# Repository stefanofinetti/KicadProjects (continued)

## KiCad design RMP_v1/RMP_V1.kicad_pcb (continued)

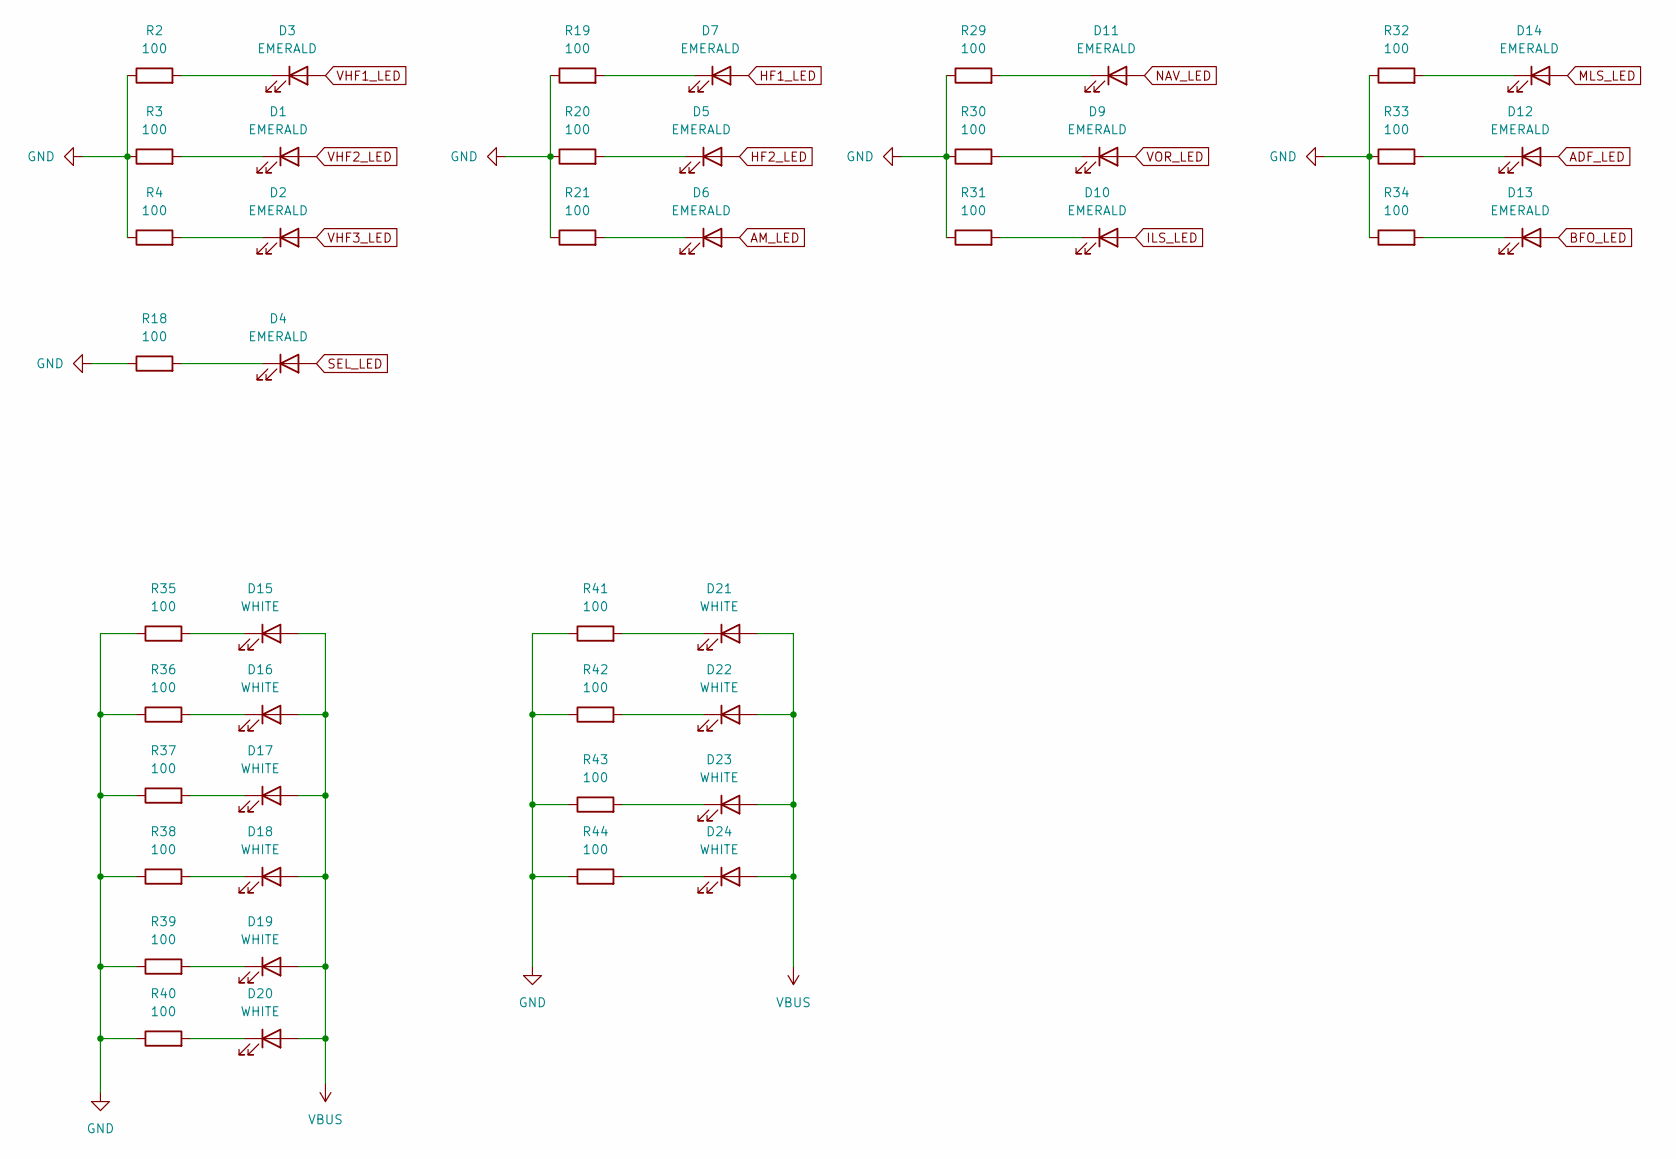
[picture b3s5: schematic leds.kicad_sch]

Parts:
D1, D2, D3, D4, D5, D6, D7, D9, D10, D11, D12, D13, D14: EMERALD; LED_0805_2012Metric
D15, D16, D17, D18, D19, D20, D21, D22, D23, D24: WHITE; LED_0603_1608Metric
R2, R3, R4, R18, R19, R20, R21, R29, R30, R31, R32, R33, R34, R35, R36, R37, R38, R39, R40, R41, R42, R43, R44: 100; R_0402_1005Metric

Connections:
ADF_LED: D12.2 (A); also elsewhere on the board
AM_LED: D6.2 (A); also elsewhere on the board
BFO_LED: D13.2 (A); also elsewhere on the board
GND: R2.1, R3.1, R4.1, R18.1, R19.1, R20.1, R21.1, R29.1, R30.1, R31.1, R32.1, R33.1, R34.1, R35.1, R36.1, R37.1, R38.1, R39.1, R40.1, R41.1, R42.1, R43.1, R44.1; also elsewhere on the board
HF1_LED: D7.2 (A); also elsewhere on the board
HF2_LED: D5.2 (A); also elsewhere on the board
ILS_LED: D10.2 (A); also elsewhere on the board
MLS_LED: D14.2 (A); also elsewhere on the board
NAV_LED: D11.2 (A); also elsewhere on the board
unnamed: D1.1 (K), R3.2
unnamed: D2.1 (K), R4.2
unnamed: D3.1 (K), R2.2
unnamed: D4.1 (K), R18.2
unnamed: D5.1 (K), R20.2
unnamed: D6.1 (K), R21.2
unnamed: D7.1 (K), R19.2
unnamed: D9.1 (K), R30.2
unnamed: D10.1 (K), R31.2
unnamed: D11.1 (K), R29.2
unnamed: D12.1 (K), R33.2
unnamed: D13.1 (K), R34.2
unnamed: D14.1 (K), R32.2
unnamed: D15.1 (K), R35.2
unnamed: D16.1 (K), R36.2
unnamed: D17.1 (K), R37.2
unnamed: D18.1 (K), R38.2
unnamed: D19.1 (K), R39.2
unnamed: D20.1 (K), R40.2
unnamed: D21.1 (K), R41.2
unnamed: D22.1 (K), R42.2
unnamed: D23.1 (K), R43.2
unnamed: D24.1 (K), R44.2
SEL_LED: D4.2 (A); also elsewhere on the board
VBUS: D15.2 (A), D16.2 (A), D17.2 (A), D18.2 (A), D19.2 (A), D20.2 (A), D21.2 (A), D22.2 (A), D23.2 (A), D24.2 (A); also elsewhere on the board
VHF1_LED: D3.2 (A); also elsewhere on the board
VHF2_LED: D1.2 (A); also elsewhere on the board
VHF3_LED: D2.2 (A); also elsewhere on the board
VOR_LED: D9.2 (A); also elsewhere on the board

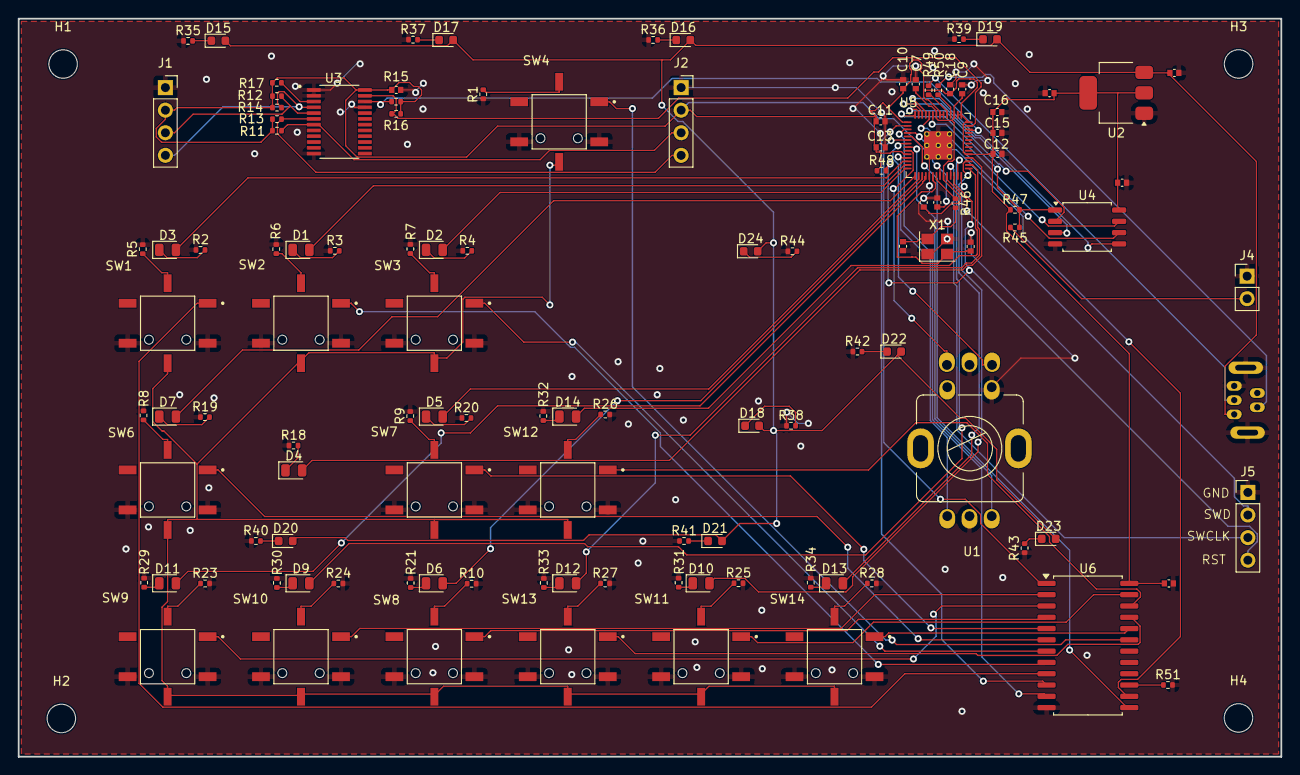
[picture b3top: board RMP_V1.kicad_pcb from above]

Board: 2 copper layers, 142.0 x 83.0 mm, 120 parts (1 on the bottom side), 101 nets.

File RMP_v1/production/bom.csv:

Designator,Footprint,Quantity,Value,LCSC Part #
"C1, C10, C11, C12, C13, C14, C15, C16, C17, C5, C7, C8",Perfect_0402,12,100nF,
"C18, C9",Perfect_0402,2,1uF,
"C2, C3",Perfect_0402,2,15pF,
"C4, C6",Perfect_0402,2,10uF,
"D1, D10, D11, D12, D13, D14, D2, D3, D4, D5, D6, D7, D9",0805,13,EMERALD,
"D15, D16, D17, D18, D19, D20, D21, D22, D23, D24",0603,10,WHITE,
J1,PinSocket_1x04_P2.54mm_Vertical,1,VHF Active OLED,
J2,PinSocket_1x04_P2.54mm_Vertical,1,VHF Standby OLED,
J3,USB_B_Mini_Amphenol_UE25BE5510H,1,USB_B_Micro,
J4,PinHeader_1x02_P2.54mm_Vertical,1,Conn_01x02,
J5,PinHeader_1x04_P2.54mm_Vertical,1,RP2040_SWD,
"R1, R10, R18, R19, R2, R20, R21, R23, R24, R25, R26, R27, R28, R29, R3, R30, R31, R32, R33, R34, R35, R36, R37, R38, R39, R4, R40, R41, R42, R43, R44, R5, R6, R7, R8, R9",0402,36,100,
"R11, R12, R13, R14, R15, R16",0402,6,4.7K,
"R17, R48, R51",0402,3,10K,
"R45, R46",0402,2,1k,
R47,0402,1,DNF,
"R49, R50",0402,2,27,
SW1,SW_TL3240F260R,1,VHF1_SW,C4364809
SW10,SW_TL3240F260R,1,VOR,C4364985
SW11,SW_TL3240F260R,1,ILS,C4364985
SW12,SW_TL3240F260R,1,MLS,C4364985
SW13,SW_TL3240F260R,1,ADF,C4364985
SW14,SW_TL3240F260R,1,BFO,C4364985
SW2,SW_TL3240F260R,1,VHF2_SW,C4364809
SW3,SW_TL3240F260R,1,VHF3_SW,C4364809
SW4,SW_TL3240F260R,1,XFER_SW,C4364985
SW6,SW_TL3240F260R,1,HF1,C4364809
SW7,SW_TL3240F260R,1,HF2,C4364809
SW8,SW_TL3240F260R,1,AM,C4364809
SW9,SW_TL3240F260R,1,NAV,C4364985
U1,EC11EBB24C03,1,ENCODER,
U2,SOT-223-3_TabPin2,1,NCP1117-3.3_SOT223,
U3,SOP65P640X120-24N,1,PCA9548APW,
U4,SOIC-8_5.23x5.23mm_P1.27mm,1,W25Q128JVS,
U5,QFN-56-1EP_7x7mm_P0.4mm_EP3.2x3.2mm,1,RP2040,
U6,SOIC-24W_7.5x15.4mm_P1.27mm,1,CD74HC4067M,
X1,Crystal_SMD_3225-4Pin_3.2x2.5mm,1,ABM8-272-T3,

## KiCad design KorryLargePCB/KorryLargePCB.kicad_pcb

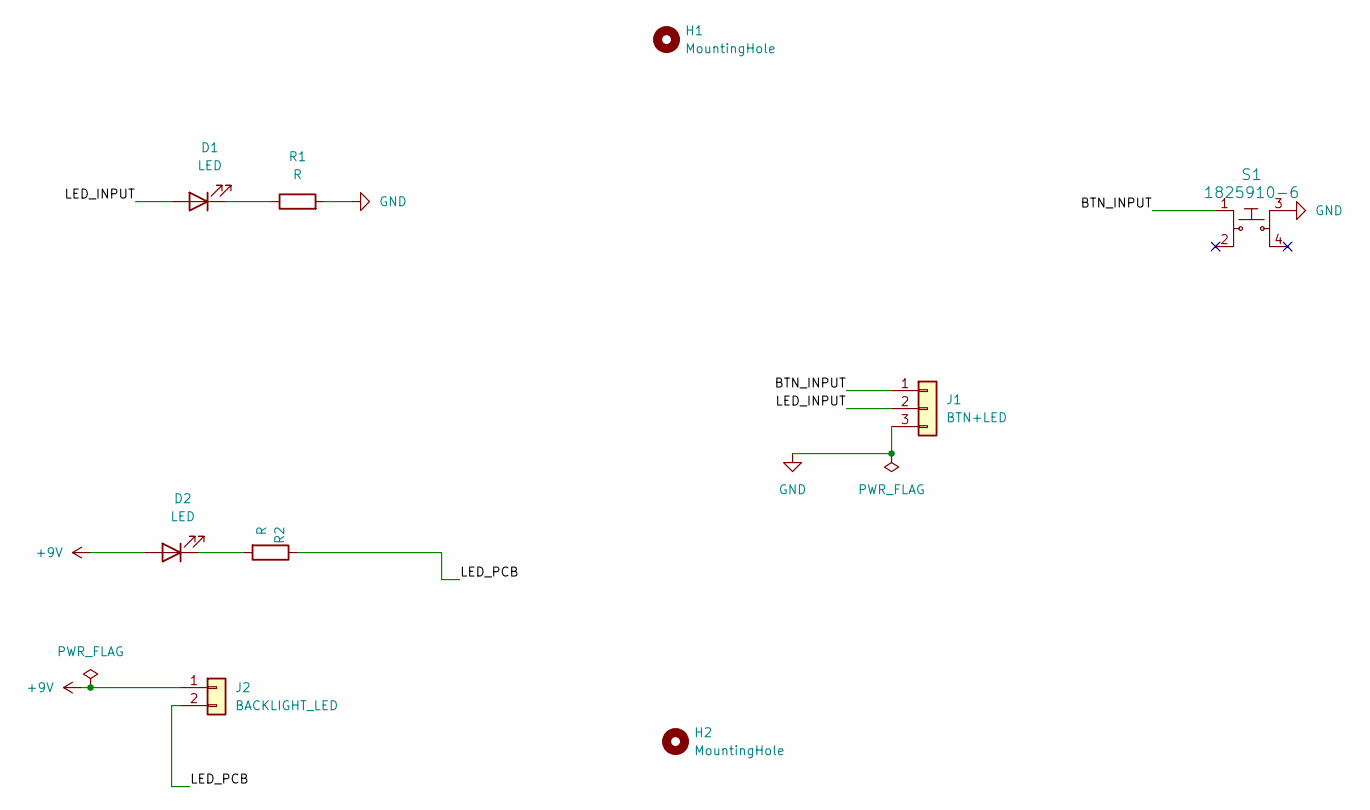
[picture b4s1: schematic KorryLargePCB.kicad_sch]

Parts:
D1, D2: LED; LED_D3.0mm
H1, H2: MountingHole; MountingHole_2.2mm_M2_DIN965_Pad_TopBottom
J1: BTN+LED; JST_EH_B3B-EH-A_1x03_P2.50mm_Vertical
J2: BACKLIGHT_LED; JST_EH_B2B-EH-A_1x02_P2.50mm_Vertical
R1, R2: R; R_Axial_DIN0207_L6.3mm_D2.5mm_P7.62mm_Horizontal
S1: 1825910-6; Switch_Tactile_THT_6x6mm; MPN 1825910-6; Digi-Key_PN 450-1650-ND

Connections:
+9V: D2.2 (A), J2.1
/BTN_INPUT: J1.1, S1.1
/LED_INPUT: D1.2 (A), J1.2
/LED_PCB: J2.2, R2.1
GND: J1.3, R1.2, S1.3
unnamed: D1.1 (K), R1.1
unnamed: D2.1 (K), R2.2

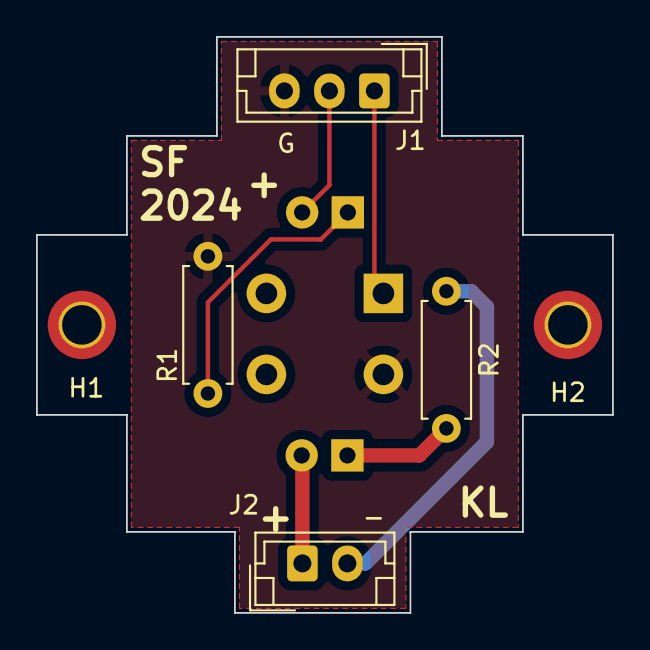
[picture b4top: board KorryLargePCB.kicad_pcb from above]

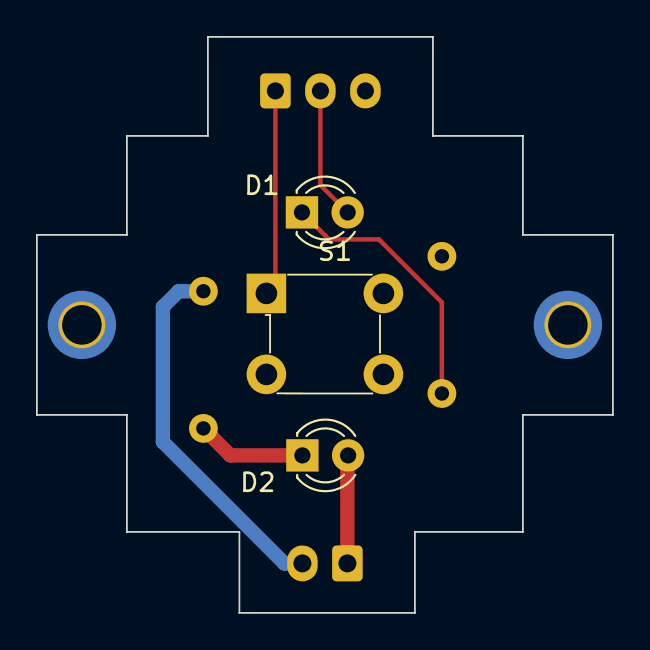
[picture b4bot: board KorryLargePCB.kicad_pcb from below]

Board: 2 copper layers, 32.0 x 32.0 mm, 9 parts (3 on the bottom side), 7 nets.

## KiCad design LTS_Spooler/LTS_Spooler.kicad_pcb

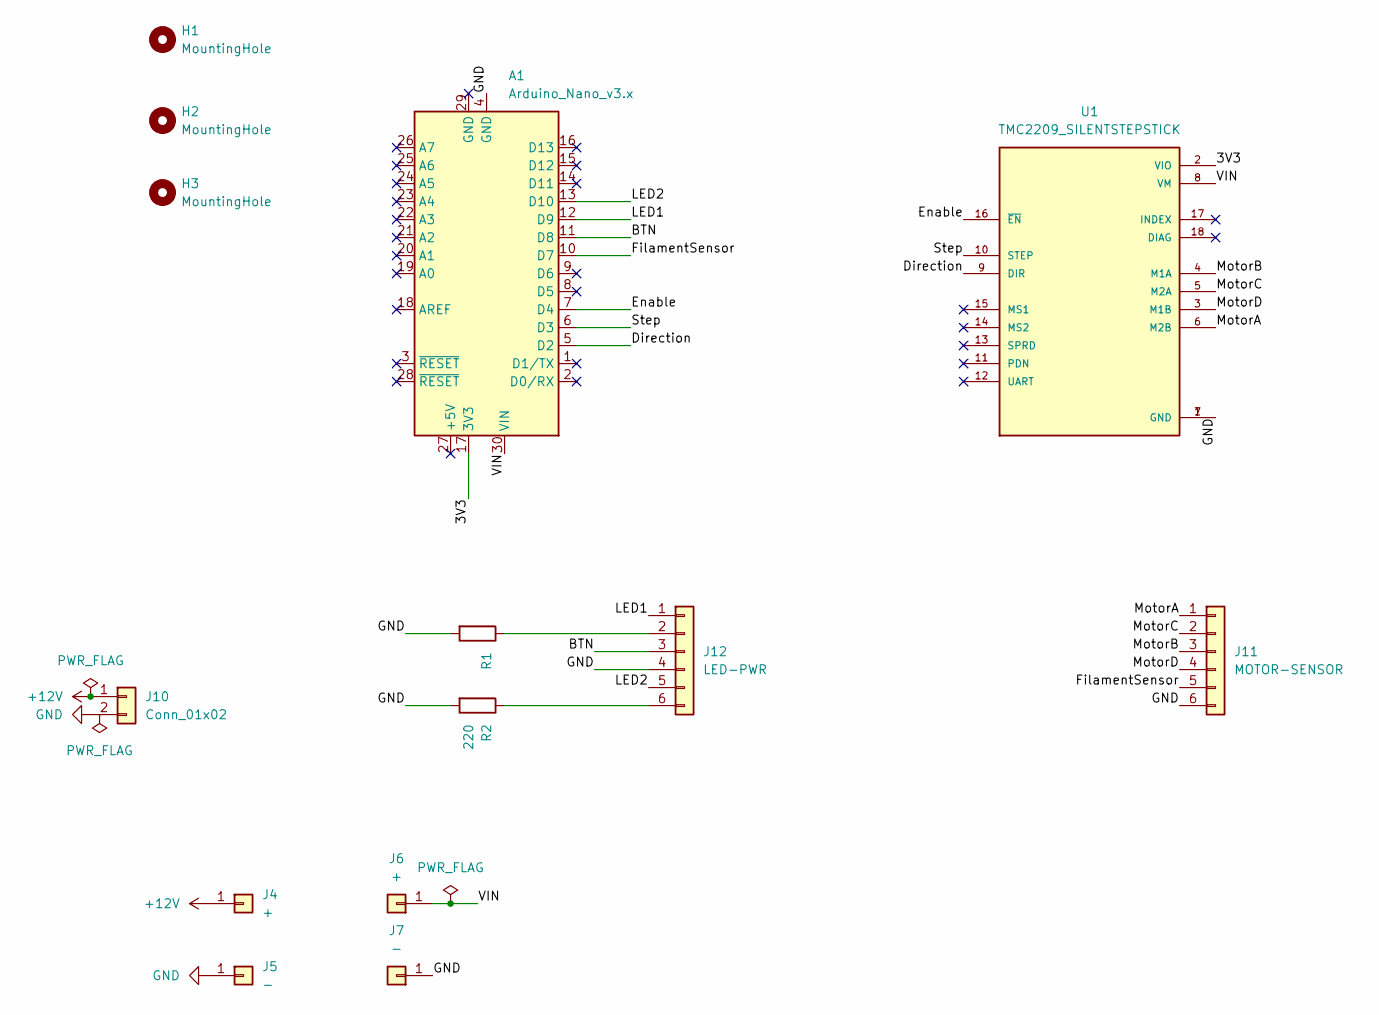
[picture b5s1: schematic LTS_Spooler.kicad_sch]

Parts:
A1: Arduino_Nano_v3.x; Arduino_Nano
H1, H2, H3: MountingHole; MountingHole_3.2mm_M3
J4, J6: +; PinHeader_1x01_P2.54mm_Vertical
J5, J7: -; PinHeader_1x01_P2.54mm_Vertical
J10: Conn_01x02; BarrelJack_Horizontal
J11: MOTOR-SENSOR; PinHeader_1x06_P2.54mm_Vertical
J12: LED-PWR; PinHeader_1x06_P2.54mm_Vertical
R1, R2: 220; R_Axial_DIN0207_L6.3mm_D2.5mm_P7.62mm_Horizontal
U1: TMC2209_SILENTSTEPSTICK; MODULE_TMC2209_SILENTSTEPSTICK; PARTREV 1.20

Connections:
+12V: J4.1, J10.1
/3V3: A1.17 (3V3), U1.2 (VIO)
/BTN: A1.11 (D8), J12.3
/Direction: A1.5 (D2), U1.9 (DIR)
/Enable: A1.7 (D4), U1.16 (~EN)
/FilamentSensor: A1.10 (D7), J11.5
/LED1: A1.12 (D9), J12.1
/LED2: A1.13 (D10), J12.5
/MotorA: J11.1, U1.6 (M2B)
/MotorB: J11.3, U1.4 (M1A)
/MotorC: J11.2, U1.5 (M2A)
/MotorD: J11.4, U1.3 (M1B)
/Step: A1.6 (D3), U1.10 (STEP)
/VIN: A1.30 (VIN), J6.1, U1.8 (VM)
GND: A1.4 (GND), J5.1, J7.1, J10.2, J11.6, J12.4, R1.2, R2.2, U1.1 (GND), U1.7 (GND)
unnamed: J12.2, R1.1
unnamed: J12.6, R2.1

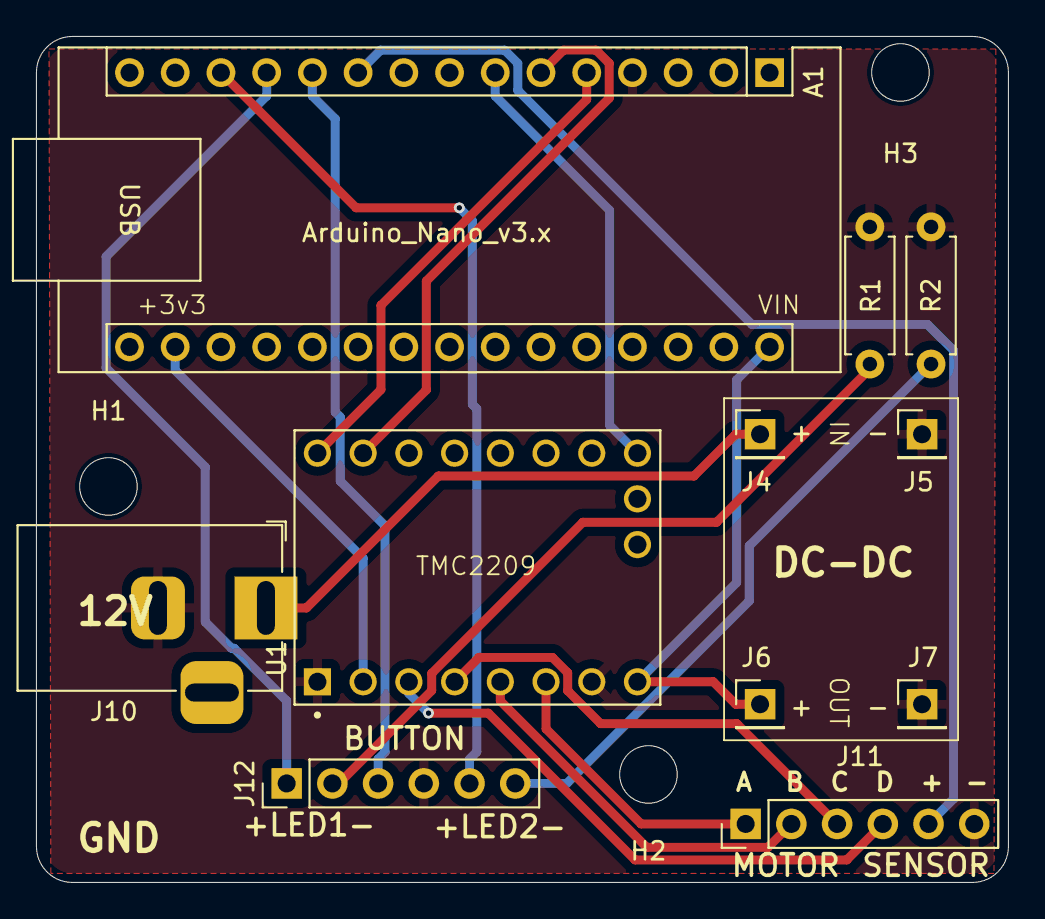
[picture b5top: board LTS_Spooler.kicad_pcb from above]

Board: 2 copper layers, 54.0 x 47.0 mm, 14 parts (0 on the bottom side), 17 nets.

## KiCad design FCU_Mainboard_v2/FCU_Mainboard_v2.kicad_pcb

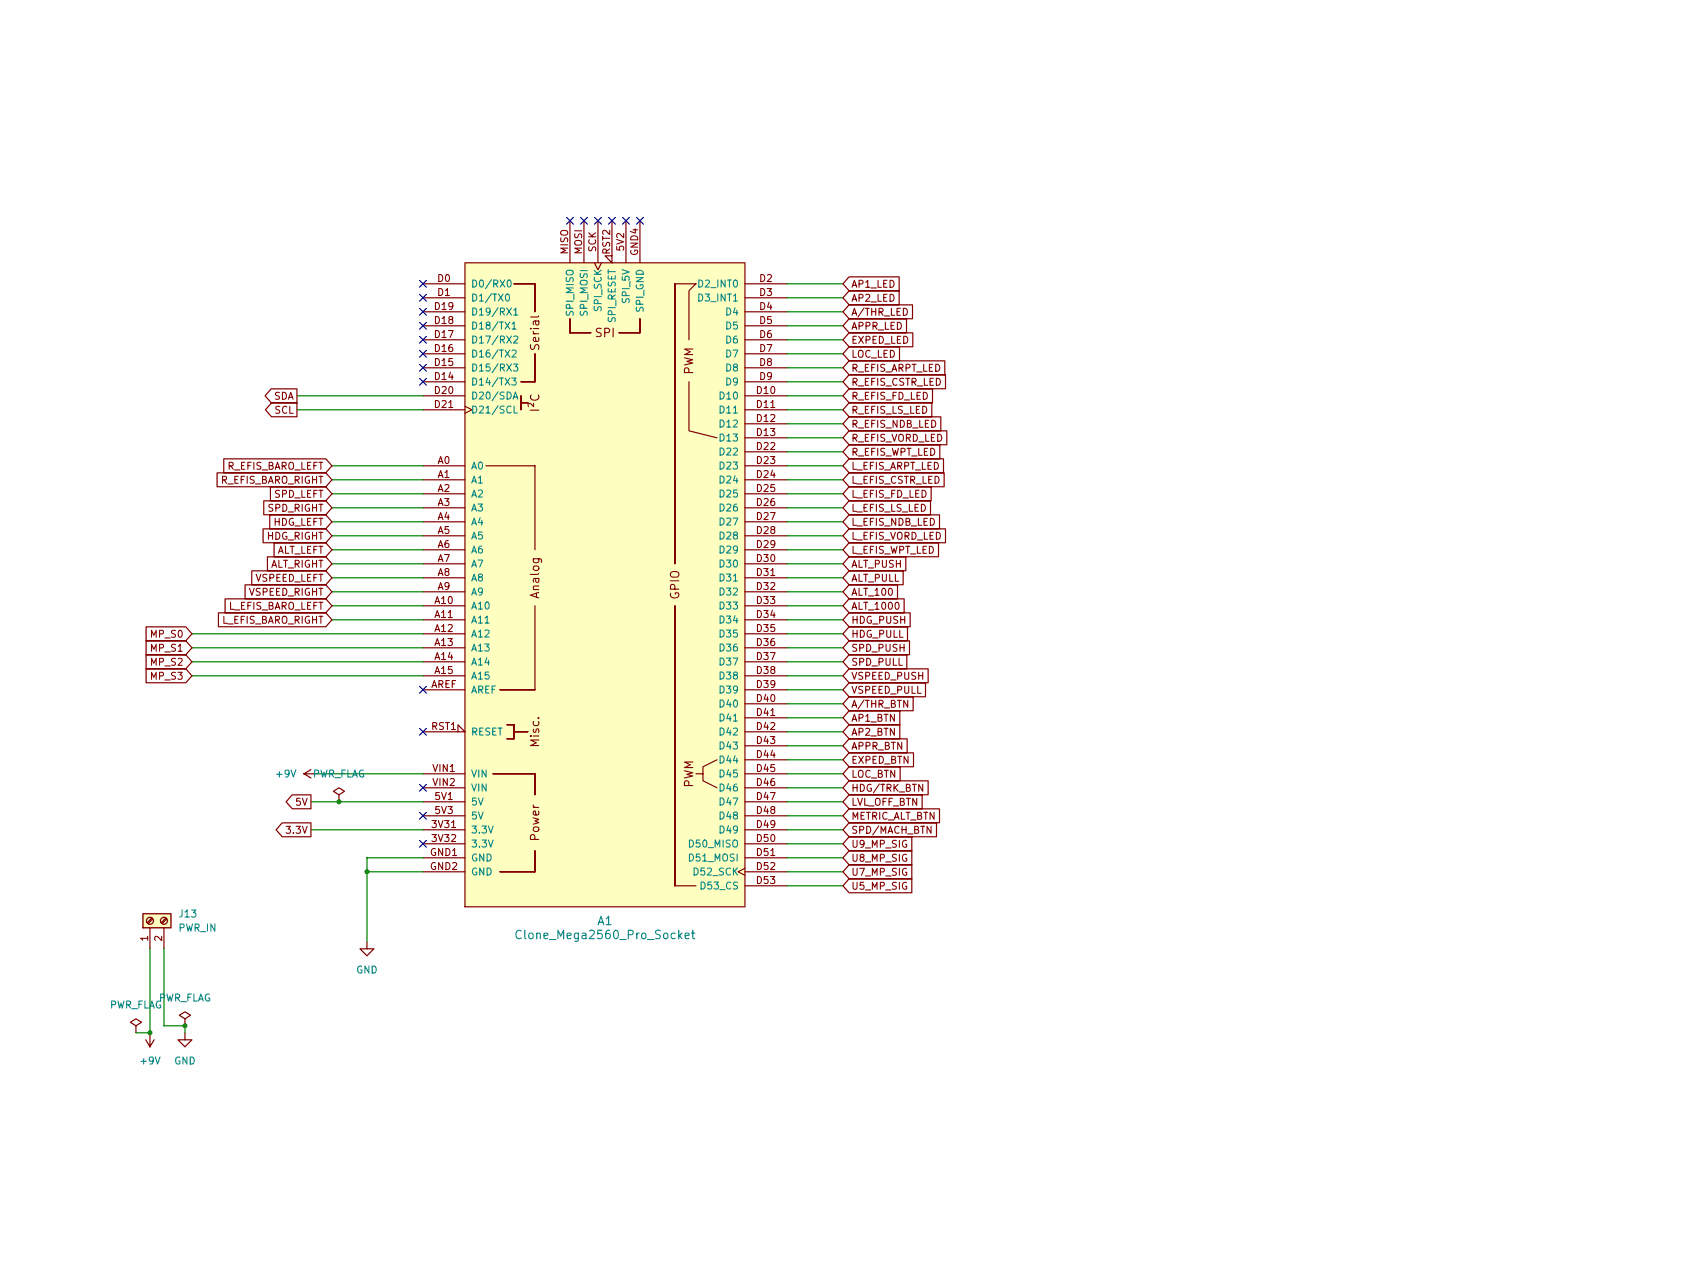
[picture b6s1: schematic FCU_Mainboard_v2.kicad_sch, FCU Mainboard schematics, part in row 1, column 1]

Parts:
A1: Clone_Mega2560_Pro_Socket
J13: PWR_IN; TerminalBlock_bornier-2_P5.08mm

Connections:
3.3V: A1.3V31 (3.3V); also elsewhere on the board
5V: A1.5V1 (5V); also elsewhere on the board
+9V: A1.VIN1 (VIN), J13.1
ALT_100: A1.D32; also elsewhere on the board
ALT_1000: A1.D33; also elsewhere on the board
ALT_LEFT: A1.A6; also elsewhere on the board
ALT_PULL: A1.D31; also elsewhere on the board
ALT_PUSH: A1.D30; also elsewhere on the board
ALT_RIGHT: A1.A7; also elsewhere on the board
AP1_BTN: A1.D41; also elsewhere on the board
AP1_LED: A1.D2 (D2_INT0); also elsewhere on the board
AP2_BTN: A1.D42; also elsewhere on the board
AP2_LED: A1.D3 (D3_INT1); also elsewhere on the board
APPR_BTN: A1.D43; also elsewhere on the board
APPR_LED: A1.D5; also elsewhere on the board
A/THR_BTN: A1.D40; also elsewhere on the board
A/THR_LED: A1.D4; also elsewhere on the board
EXPED_BTN: A1.D44; also elsewhere on the board
EXPED_LED: A1.D6; also elsewhere on the board
GND: A1.GND1 (GND), A1.GND2 (GND), J13.2; also elsewhere on the board
HDG_LEFT: A1.A4; also elsewhere on the board
HDG_PULL: A1.D35; also elsewhere on the board
HDG_PUSH: A1.D34; also elsewhere on the board
HDG_RIGHT: A1.A5; also elsewhere on the board
HDG/TRK_BTN: A1.D46; also elsewhere on the board
LOC_BTN: A1.D45; also elsewhere on the board
LOC_LED: A1.D7; also elsewhere on the board
LVL_OFF_BTN: A1.D47; also elsewhere on the board
L_EFIS_ARPT_LED: A1.D23; also elsewhere on the board
L_EFIS_BARO_LEFT: A1.A10; also elsewhere on the board
L_EFIS_BARO_RIGHT: A1.A11; also elsewhere on the board
L_EFIS_CSTR_LED: A1.D24; also elsewhere on the board
L_EFIS_FD_LED: A1.D25; also elsewhere on the board
L_EFIS_LS_LED: A1.D26; also elsewhere on the board
L_EFIS_NDB_LED: A1.D27; also elsewhere on the board
L_EFIS_VORD_LED: A1.D28; also elsewhere on the board
L_EFIS_WPT_LED: A1.D29; also elsewhere on the board
METRIC_ALT_BTN: A1.D48; also elsewhere on the board
MP_S0: A1.A12; also elsewhere on the board
MP_S1: A1.A13; also elsewhere on the board
MP_S2: A1.A14; also elsewhere on the board
MP_S3: A1.A15; also elsewhere on the board
R_EFIS_ARPT_LED: A1.D8; also elsewhere on the board
R_EFIS_BARO_LEFT: A1.A0; also elsewhere on the board
R_EFIS_BARO_RIGHT: A1.A1; also elsewhere on the board
R_EFIS_CSTR_LED: A1.D9; also elsewhere on the board
R_EFIS_FD_LED: A1.D10; also elsewhere on the board
R_EFIS_LS_LED: A1.D11; also elsewhere on the board
R_EFIS_NDB_LED: A1.D12; also elsewhere on the board
R_EFIS_VORD_LED: A1.D13; also elsewhere on the board
R_EFIS_WPT_LED: A1.D22; also elsewhere on the board
SCL: A1.D21 (D21/SCL); also elsewhere on the board
SDA: A1.D20 (D20/SDA); also elsewhere on the board
SPD_LEFT: A1.A2; also elsewhere on the board
SPD_PULL: A1.D37; also elsewhere on the board
SPD_PUSH: A1.D36; also elsewhere on the board
SPD_RIGHT: A1.A3; also elsewhere on the board
SPD/MACH_BTN: A1.D49; also elsewhere on the board
U5_MP_SIG: A1.D53 (D53_CS); also elsewhere on the board
U7_MP_SIG: A1.D52 (D52_SCK); also elsewhere on the board
U8_MP_SIG: A1.D51 (D51_MOSI); also elsewhere on the board
U9_MP_SIG: A1.D50 (D50_MISO); also elsewhere on the board
VSPEED_LEFT: A1.A8; also elsewhere on the board
VSPEED_PULL: A1.D39; also elsewhere on the board
VSPEED_PUSH: A1.D38; also elsewhere on the board
VSPEED_RIGHT: A1.A9; also elsewhere on the board

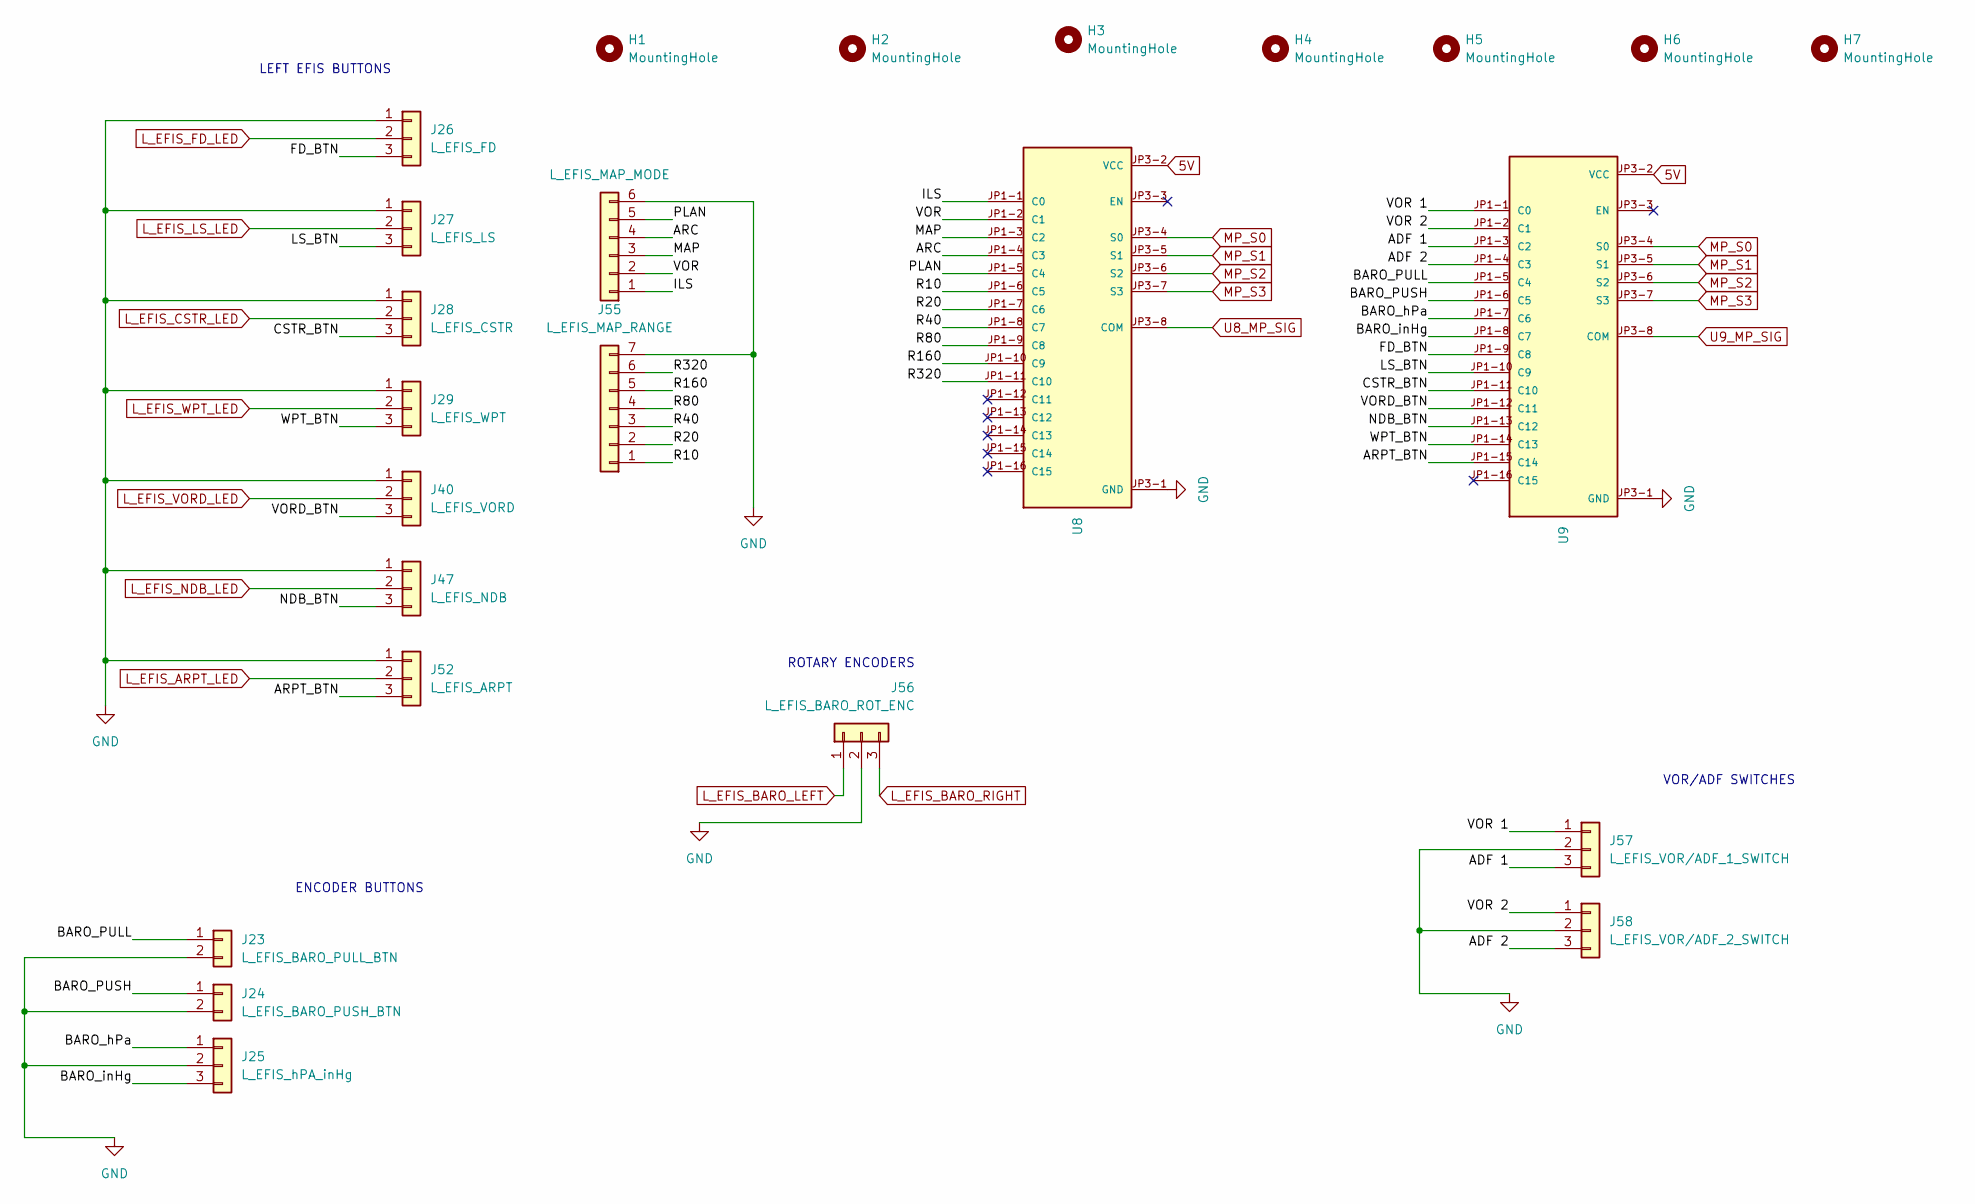
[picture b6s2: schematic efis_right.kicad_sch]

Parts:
H1, H2, H3, H4, H5, H6, H7: MountingHole; MountingHole_2.2mm_M2_DIN965_Pad_TopBottom
J23: L_EFIS_BARO_PULL_BTN; JST_EH_B2B-EH-A_1x02_P2.50mm_Vertical
J24: L_EFIS_BARO_PUSH_BTN; JST_EH_B2B-EH-A_1x02_P2.50mm_Vertical
J25: L_EFIS_hPA_inHg; JST_EH_B3B-EH-A_1x03_P2.50mm_Vertical
J26: L_EFIS_FD; JST_EH_B3B-EH-A_1x03_P2.50mm_Vertical
J27: L_EFIS_LS; JST_EH_B3B-EH-A_1x03_P2.50mm_Vertical
J28: L_EFIS_CSTR; JST_EH_B3B-EH-A_1x03_P2.50mm_Vertical
J29: L_EFIS_WPT; JST_EH_B3B-EH-A_1x03_P2.50mm_Vertical
J40: L_EFIS_VORD; JST_EH_B3B-EH-A_1x03_P2.50mm_Vertical
J47: L_EFIS_NDB; JST_EH_B3B-EH-A_1x03_P2.50mm_Vertical
J52: L_EFIS_ARPT; JST_EH_B3B-EH-A_1x03_P2.50mm_Vertical
J54: L_EFIS_MAP_MODE; JST_EH_B6B-EH-A_1x06_P2.50mm_Vertical
J55: L_EFIS_MAP_RANGE; JST_EH_B7B-EH-A_1x07_P2.50mm_Vertical
J56: L_EFIS_BARO_ROT_ENC; JST_EH_B3B-EH-A_1x03_P2.50mm_Vertical
J57: L_EFIS_VOR/ADF_1_SWITCH; JST_EH_B3B-EH-A_1x03_P2.50mm_Vertical
J58: L_EFIS_VOR/ADF_2_SWITCH; JST_EH_B3B-EH-A_1x03_P2.50mm_Vertical
U8, U9: Multiplexer CD74HC4067 Breakout; MODULE_BOB-09056; PARTREV v11

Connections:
5V: U8.JP3-2 (VCC), U9.JP3-2 (VCC); also elsewhere on the board
/EFIS_RIGHT/ADF 1: J57.3, U9.JP1-3 (C2)
/EFIS_RIGHT/ADF 2: J58.3, U9.JP1-4 (C3)
/EFIS_RIGHT/ARC: J54.4, U8.JP1-4 (C3)
/EFIS_RIGHT/ARPT_BTN: J52.3, U9.JP1-15 (C14)
/EFIS_RIGHT/BARO_PULL: J23.1, U9.JP1-5 (C4)
/EFIS_RIGHT/BARO_PUSH: J24.1, U9.JP1-6 (C5)
/EFIS_RIGHT/BARO_hPa: J25.1, U9.JP1-7 (C6)
/EFIS_RIGHT/BARO_inHg: J25.3, U9.JP1-8 (C7)
/EFIS_RIGHT/CSTR_BTN: J28.3, U9.JP1-11 (C10)
/EFIS_RIGHT/FD_BTN: J26.3, U9.JP1-9 (C8)
/EFIS_RIGHT/ILS: J54.1, U8.JP1-1 (C0)
/EFIS_RIGHT/LS_BTN: J27.3, U9.JP1-10 (C9)
/EFIS_RIGHT/MAP: J54.3, U8.JP1-3 (C2)
/EFIS_RIGHT/NDB_BTN: J47.3, U9.JP1-13 (C12)
/EFIS_RIGHT/PLAN: J54.5, U8.JP1-5 (C4)
/EFIS_RIGHT/R10: J55.1, U8.JP1-6 (C5)
/EFIS_RIGHT/R20: J55.2, U8.JP1-7 (C6)
/EFIS_RIGHT/R40: J55.3, U8.JP1-8 (C7)
/EFIS_RIGHT/R80: J55.4, U8.JP1-9 (C8)
/EFIS_RIGHT/R160: J55.5, U8.JP1-10 (C9)
/EFIS_RIGHT/R320: J55.6, U8.JP1-11 (C10)
/EFIS_RIGHT/VOR: J54.2, U8.JP1-2 (C1)
/EFIS_RIGHT/VOR 1: J57.1, U9.JP1-1 (C0)
/EFIS_RIGHT/VOR 2: J58.1, U9.JP1-2 (C1)
/EFIS_RIGHT/VORD_BTN: J40.3, U9.JP1-12 (C11)
/EFIS_RIGHT/WPT_BTN: J29.3, U9.JP1-14 (C13)
GND: J23.2, J24.2, J25.2, J26.1, J27.1, J28.1, J29.1, J40.1, J47.1, J52.1, J54.6, J55.7, J56.2, J57.2, J58.2, U8.JP3-1 (GND), U9.JP3-1 (GND); also elsewhere on the board
L_EFIS_ARPT_LED: J52.2; also elsewhere on the board
L_EFIS_BARO_LEFT: J56.1; also elsewhere on the board
L_EFIS_BARO_RIGHT: J56.3; also elsewhere on the board
L_EFIS_CSTR_LED: J28.2; also elsewhere on the board
L_EFIS_FD_LED: J26.2; also elsewhere on the board
L_EFIS_LS_LED: J27.2; also elsewhere on the board
L_EFIS_NDB_LED: J47.2; also elsewhere on the board
L_EFIS_VORD_LED: J40.2; also elsewhere on the board
L_EFIS_WPT_LED: J29.2; also elsewhere on the board
MP_S0: U8.JP3-4 (S0), U9.JP3-4 (S0); also elsewhere on the board
MP_S1: U8.JP3-5 (S1), U9.JP3-5 (S1); also elsewhere on the board
MP_S2: U8.JP3-6 (S2), U9.JP3-6 (S2); also elsewhere on the board
MP_S3: U8.JP3-7 (S3), U9.JP3-7 (S3); also elsewhere on the board
U8_MP_SIG: U8.JP3-8 (COM); also elsewhere on the board
U9_MP_SIG: U9.JP3-8 (COM); also elsewhere on the board

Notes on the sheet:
LEFT EFIS BUTTONS
ROTARY ENCODERS
ENCODER BUTTONS
VOR/ADF SWITCHES

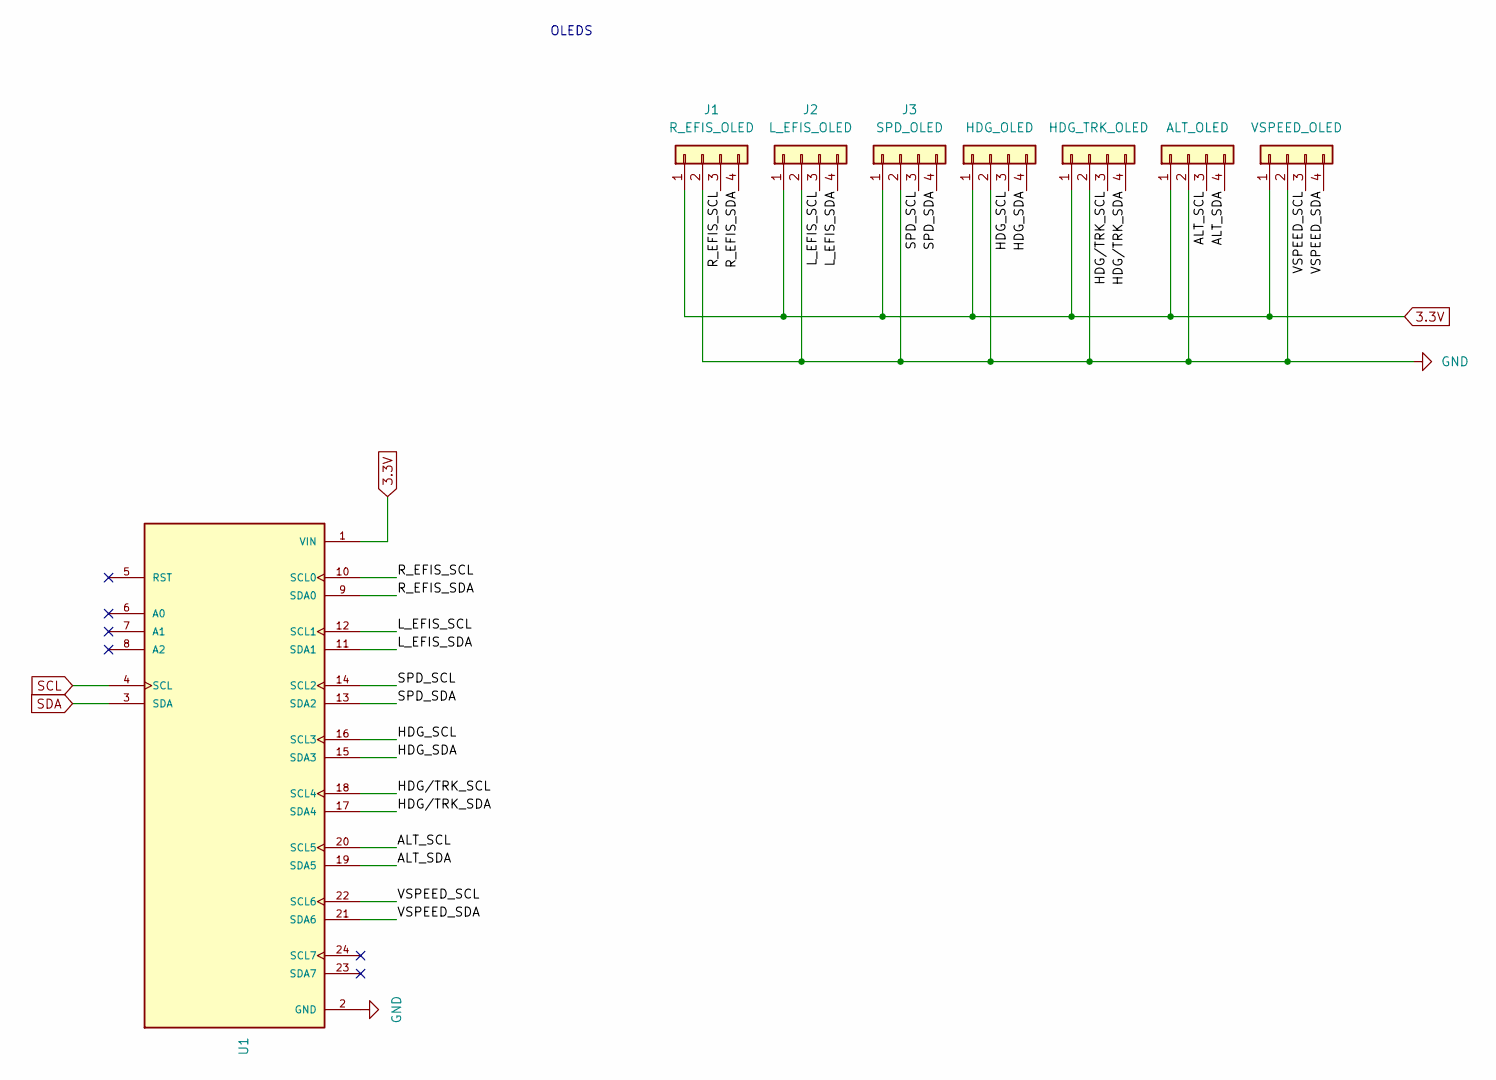
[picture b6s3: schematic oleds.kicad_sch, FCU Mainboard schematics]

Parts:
J1: R_EFIS_OLED; JST_EH_B4B-EH-A_1x04_P2.50mm_Vertical
J2: L_EFIS_OLED; JST_EH_B4B-EH-A_1x04_P2.50mm_Vertical
J3: SPD_OLED; JST_EH_B4B-EH-A_1x04_P2.50mm_Vertical
J4: HDG_OLED; JST_EH_B4B-EH-A_1x04_P2.50mm_Vertical
J5: HDG_TRK_OLED; JST_EH_B4B-EH-A_1x04_P2.50mm_Vertical
J14: ALT_OLED; JST_EH_B4B-EH-A_1x04_P2.50mm_Vertical
J15: VSPEED_OLED; JST_EH_B4B-EH-A_1x04_P2.50mm_Vertical
U1: Adafruit TCA4598A; MODULE_2717; PARTREV Sep 11, 2015

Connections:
3.3V: J1.1, J2.1, J3.1, J4.1, J5.1, J14.1, J15.1, U1.1 (VIN); also elsewhere on the board
/OLEDs/ALT_SCL: J14.3, U1.20 (SCL5)
/OLEDs/ALT_SDA: J14.4, U1.19 (SDA5)
/OLEDs/HDG_SCL: J4.3, U1.16 (SCL3)
/OLEDs/HDG_SDA: J4.4, U1.15 (SDA3)
/OLEDs/HDG/TRK_SCL: J5.3, U1.18 (SCL4)
/OLEDs/HDG/TRK_SDA: J5.4, U1.17 (SDA4)
/OLEDs/L_EFIS_SCL: J2.3, U1.12 (SCL1)
/OLEDs/L_EFIS_SDA: J2.4, U1.11 (SDA1)
/OLEDs/R_EFIS_SCL: J1.3, U1.10 (SCL0)
/OLEDs/R_EFIS_SDA: J1.4, U1.9 (SDA0)
/OLEDs/SPD_SCL: J3.3, U1.14 (SCL2)
/OLEDs/SPD_SDA: J3.4, U1.13 (SDA2)
/OLEDs/VSPEED_SCL: J15.3, U1.22 (SCL6)
/OLEDs/VSPEED_SDA: J15.4, U1.21 (SDA6)
GND: J1.2, J2.2, J3.2, J4.2, J5.2, J14.2, J15.2, U1.2 (GND); also elsewhere on the board
SCL: U1.4 (SCL); also elsewhere on the board
SDA: U1.3 (SDA); also elsewhere on the board

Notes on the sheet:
OLEDS
